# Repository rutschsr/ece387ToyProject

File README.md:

# ECE 387 Individual Final Project
## Overview
This useless box is entirely 3D printed and uses a Arduino Micro (ATMEGA 32U) programmed in C using AVR-GCC and AVRDUDE. 

The operation of the Useless Box toy is very simple ... there are two switches, and when each of them are turned on, an arm emerges from inside the box and turns it back off. Therefore the Useless Box serves no real function: it is "useless".

## Operational Demonstration

## Operational Overview

The Useless box is a simple toy; it turns the switch off when it is turned on by a user. 

## 3D Printed Parts

I designed all of the mechanical parts for the Useless Box in Autodesk Fusion 360. All of the design files are located in this [Folder](https://github.com/rutschsr/ece387ToyProject/tree/main/3-D%20Parts). Each part was "sliced" (split into layers and 3D printer gcode) using [Utlimaker Cura](https://ultimaker.com/software/ultimaker-cura). I then printed each of the pieces on my Creality Ender 3 V2 3D printer using PLA (polyactic acid) filament. Each piece is is hollow and includes between 40 and 60% fill in a triangular manner to reduce print time and increase strength.

### Box Bottom

Box in Autodesk Fusion 360. I exported the drawing to Utilimaker Cura to "slice" it before it was printed.

A raspberry pi running Octoprint is connected to my printer which provides a web interface to upload drawings and control the printer from. This printer is connected to the raspberry pi using a micro usb cable.

The bottom of the box used nearly the entire print volume of the printer, took approximately 22 hours to complete, and used approximately 200g ($4-5) of material.

### Box Top

The top of the Useless box, still on the printer. The larger holes are where the switches are mounted, and the smaller holes are screw holes.

### Box Door

The box with hinge mounts on the printer. The raised area on the bottom was originally planned to be a rubber band mount to close the door, but this was not necessary as the door closes by itself.

### Servo Mount

The original small servo mount with a servo motor. This motor did not have enough torque and was replaced with a larger motor. The design of the Servo mount stayed the same design but was slightly larger.

### Servo Arm

The brackets and arms also took some trial and error to get correct. The larger servo motors meant that the arms had to be offset to turn off the switches, as the box was not wide enough. This was the only real design change with the arm. I used screws to attach the arm to a mount that came with the servo. This just relies on friction between the gears to stay.

## Assembly

Servo Motors mounted inside The Box with switches and offset arms installed. From this view the width of the servo motors and box that required the arms to offset can be seen.

Assembled box with the door open.

## Wiring and Connections

Above is the Schematic Diagram showing the connections for the Useless Box.

My Useless Box accepts a 5-7 V input on either the VIN jack on the outside of the box near the power switch, or the internal battery box which holds four AA batteries.

Internally, the servo motors are powered directly from the VIN port with no voltage regulation and this is why the input is limited to 7 volts. The Arduino Micro is then powered through its VIN pin. On the Arduino two digital input pins are used for the switches, and two PWM pins are used to control the servos. The wiring is very simple, with the only components being the servo motors, the switches, and bleed resistors for the switches.

All of the connections are soldered or socketed to improve the reliability. I used a solder perfboard to attach all of the components and header pins for the Arduino and Servo motors.

The Servo headers are on the bottom left of the perfboard, while the black 4 wire cable goes to the switches mounted on the top of the box. After I soldered the components on to the perfboard I used hotglue on all connections to ensure the wires do not break off at their connections.

## Issues

There were several issues and design changes while building the Useless Box. The first was my original choice for servo motor was very small 9g servo motors. After adding a large arm to be able to reach the switch, the motors did not have enough torque to turn the switches off. I than purchased some 20g replacement servos that are much larger and have much more torque. This required other design changes, however. Since the new motors were larger I had to redesign both the servo mounts and the servo arms. The mounts had to sit lower and be longer to fit the larger motor. The Servo arms had to have an offset so the arm would line up with a switch.

Another issue I experienced was with the Arduino. Originally I planned on using an Arduino Uno clone that I had been gifted several years ago. This has the same ATMEGA A328P on the official Arduino Uno, but as is common with the clones, does not have isolation between the USB power supply and board power supply. I found this out the hard way, by having power from my bench power supply applied through the VIN pin and USB power connected for programming. The ATMEGA microcontroller kept functioning but the USB controller failed and lost the ability to communicate. I then switched to a Arduino micro I had sitting around in preperation for a different project which fits much better inside the box but had its own challenges, such as the surface mounted micro USB programming port I managed to tear off the board almost immediately. Thankfully this was easily fixed with some solder and a few minutes of time. The real issue with the Arduino Micro came when it was time to program it in C. Those issues are explained in more detail in the C code section.

The final issue I had was following the input voltage requirements for the Servo motors. Since the servo motors are connected to the VIN connection and voltage is not regulated the voltage must stay within the servo's voltage rating of 4.0-7.2V even though the Arduino is rated for higher voltage. Unfortunately, I did not follow this and connected the Useless box to a 12V power supply I have with the same barrel jack. This did not immediately cause a failure, but one of the servos did eventually fail (and let the smoke out). I replaced the servo with a spare and it has been functioning correctly (at the correct, 5V input) since.

## Arduino Programming

The Arduino (C++) program I used for testing started with the Arduino example code for sweeping the servo motor. It is modified to move the servo motors based on the switch position. The code is located in the [Arduino Folder](https://github.com/rutschsr/ece387ToyProject/tree/main/Arduino/SimpleTest). It uses two counters in the repeating loop part of the program to sweep each of the servos up when the switch was on, and then sweep it down when it was off. This required two for loops as since the servos are sitting opposite each other, they are rotating in the opposite direction. Also included in this code was code to check that the desired position for the Servos was not exceeding what it needed to in order to turn the switches off. This is important because occassionally the arm gets stuck without turning the switch off, especially if the user is being rough with it. If this motor would get stuck it would put a large amount of stress on the mechanical compoenents and servo motors while also having other unexpected behavior. The counter would count until it overflowed, and then the desired Servo position would become very negative, which also is not desired. The Arduino code also just uses the Arduino Servo library and the Servo.write() method to write the desired location to the servo.

## C code

Although not required for this assignment I chose to challenge myself and implement the code in bare metal C code as well. I experienced two main challenges with this; programming the Arduino Micro Atmega A32U from AVRDUDE, since it operates differently then the A328P and implementing PWM on it, since the counters and registers are different then the A328P. The C code is located in the [src folder](https://github.com/rutschsr/ece387ToyProject/tree/main/src). I used the same python script as the labs to compile and program the arduino, although some modifications to the settings for AVR-GCC and avrdude had to be made to accomidate the ATMEGA A32U.

Programming the A32U from AVRDUDE initially proved to be a challenge but I was eventually able to figure out a procedure that was reliable. As with other labs, I started programming using AVRDUDE in an Ubuntu Virtual machine with the Arduino connection passed through from my Windows laptop. This was unreliable because of the procedure for programming, so eventually I decided to program the Arduino solely from a spare laptop I have that runs Ubuntu natively. 

The Arduino Micro's Atmega A32U microcontroller requires a very specific set of steps to be followed. The reset button must be pushed on the board (The Arduino IDE implements this somehow in software, but I was unable to). Then there are 8 seconds to do the remaining steps: The serial port the Arduino is attatched to must be opened at a rate of 1200bps and then immidiatley closed. I accomplished this by using the serial monitor in the Arduino IDE. Then finally the script that compiles and programs the Arduino using avr-gcc and AVRDUDE must be run. This procedure on the native linux machine had a very high success rate.

The second large issue with programming in C was implementing PWM on the A32U in the Arduino Micro. The registers and counters used for PWM on the A32U are different than those used in the Atmega A328P we used in the labs. I first tried to set up PWM the same was using the different counter configuration for the A32U but this proved time consuming and did not work. I was Thankfully able to find help [Online](https://extremeelectronics.co.in/avr-tutorials/servo-motor-control-by-using-avr-atmega32-microcontroller/) where others had implemented PWM on the Atmega A32U.

With those two issues solved, the rest of the C code is essentially ported from the Arduino Code version. The only differences are syntax and the obvious lack of the Servo.write() method. The C-Code version of the code is what is used for the demonstration video.

## Power Reduction Techniques:
As this project can be battery powered, power reduction techniques are necessary to ensure a long battery life. The useless box can be powered by 4AA batteries in a battery case that is under the useless box door. The box's ATMEGA A32U microcontroller - integrated into the Arduino Micro, is programmed using baremetal C in order to reduce the overhead and power consumption. This also uses direct manipulation of counters for PWM control so any overhead required by the Arduino libraries was eliminated. The battery life is still quite poor however, as the Servo motors can draw approximately 1 amp each under load. When operating under battery power, the AA batteries cannot output 2A for a long period of time, so battery life is poor.

## Improvements:
As with any project, by the time it was finished there were several things that I would do differently if I were to do the project again. One of these changes would be further improving the power consumption. Even with the power reduction techniques described above the power consumption and battery life are still rather poor. One easy power reduction technique I would employ if starting again is controlling the power to the servo motors using a MOSFET, so they would only have power when they are active and have a reason to be moving. Another power reduction technique I would have employed is using interrupts for the switch control, so the microcontroller could be in a ultra low power state when niether of the servos are moving. Finally instead of using the Arduino micro with the ATMEGA 32U microcontroller, I likely would use a bare ATMEGA A328P for the better packaging and power consumption.

Other power improvments for the box could include a rechargable battery system. A rechargable lithium battery could be implemented into the system power it for longer periods of time. This also could be implemented with a USB power source to easier find a power source versus the DC barrel jack on the current Useless Box. As a sidenote, the barrel jack is necessary without a permanant onboard battery due to the high power requirements of the servos that a USB power supply (especially a computer) cannot support.

Mechanical improvements I would make if I were starting again would be to design the bottom of the box with the servo mounts intergrated. This would increase the servo mounts structual integrity, would reduce their movement, and remove the need for the hot glue I added to keep the motors from moving. I also would use screws to mount the servo "arms" to the servo motors instead of relying on friction of the gears to work. While designing the initial bottom of the box I should have also considered the motion of the door opening so that I would not have had to knotch the door on the sides to let it open. This was the first project I had completed with 3-D printed parts and Fusion 360, so it was a learning expierence both with the 3-D design software and my 3-D printer.

## Cost

Cost breakdown. Costs for 3D printed parts are estimated from the slicer's estimate of the filament required for printing.

| Part | Quantity | Cost | Note |
| --- | ----------- | --- | --- |
| Box Bottom | 1 | $5.74 | PLA |
| Box Top | 1 | $1.10 | PLA |
| Box Door | 1 | $1.02 | PLA |
| Servo Arms | 2 | $0.55 | PLA |
| Servo Mounts | 2 | $0.55 | PLA |
| Original Servos| 2 | $10.99 |  |
| Larger Servos| 2 | $22.35 |  |
| Switches | 2 | $1.60 |  |
| Arduino Micro | 1 | $21.00 |  |
| Perfboard | 1 | $6.99 | Adafruit |
| Hinge Rod | 1 | $8.51 |  |
| Miscelaneous | N/A | $5 | Other Various Parts |

Total: $85.40

## More Information:

Additional Documentation found at: https://srutschilling.net/ECE387/ToyProject/

(Site will be undergoing maintenance between May 15-June 1 2022)

Additional help with PWM on ATMEGA 32U from: https://extremeelectronics.co.in/avr-tutorials/servo-motor-control-by-using-avr-atmega32-microcontroller/

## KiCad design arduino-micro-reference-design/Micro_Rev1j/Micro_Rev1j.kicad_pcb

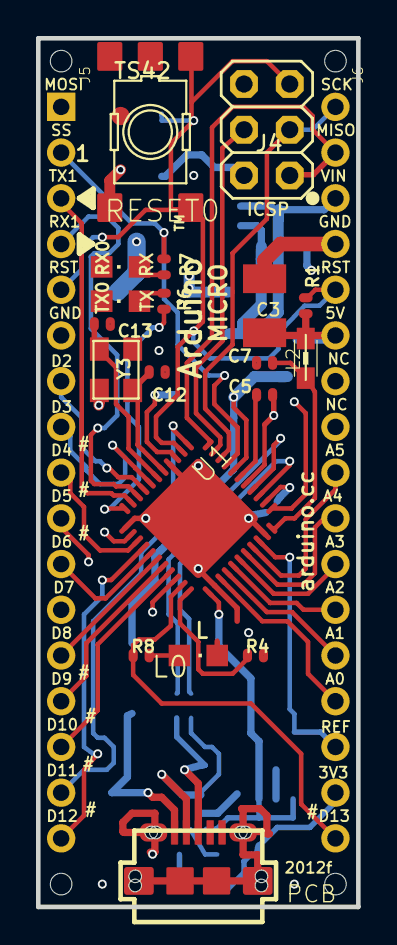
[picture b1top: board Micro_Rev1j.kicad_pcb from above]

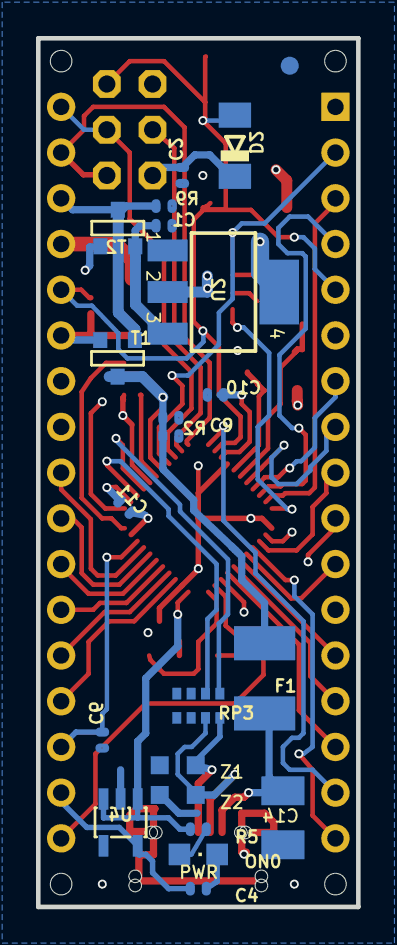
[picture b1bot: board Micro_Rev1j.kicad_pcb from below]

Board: 4 copper layers, 17.8 x 48.3 mm, 49 parts (22 on the bottom side), 47 nets.

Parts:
@HOLE0, @HOLE1, @HOLE2, @HOLE3: (no value)
C1, C2, C6, C9, C10, C11: 100n; C0402
C3, C14: 22u; SMC_B
C4, C5, C7: 1uF; C0402
C12, C13: 22pF; C0402
D2: CD1206-S01575; MINIMELF
F1: MF-MSMF050-2 500mA; L1812
FRAME1: DNP; FRAME
J3: USB-MICRO!!!; CON2_USB_MICRO_B_AT
J4: 3x2M; 2X03
J5: HEAD17-NOSS
J6: HEAD17-NOSS-1
L0: green; CHIPLED_0805
L2: MH2029-300Y; 0805
ON0: blue; CHIPLED_0805
R1, R2, R4, R9: 10K; R0402
R5, R6, R7, R8: 1K; R0402
RESET0: TS42
RP3: 22R; CAY16
RX0: yellow; CHIPLED_0805
T1: FDN340P/PMV48XP; SOT-23
T2: PMV48XP; SOT-23
TX0: yellow; CHIPLED_0805
U1: ATMEGA32U4-XUMU; QFN44ML7X7
U2: NCP1117-5; SOT223
U4: LP2985-33DBVR; SOT23-DBV
U$37: FIDUCIALMOUNT; FIDUCIA-MOUNT
U$53: FIDUCIAL1X2; FIDUCIAL-1X2
Y3: 16MHz KX-7; CRYSTAL-3.2-2.5
Z1, Z2: CG0603MLC-05E; CT_CN0603

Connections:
3V3: C4.1, J6.16, U4.5
+5V: C2.1, C3.+, C10.1, C11.1, D2.C, J4.2, J6.6, L2.1, R1.1, R5.1, T1.2, T2.3, U1.2, U1.14, U1.24, U1.34, U2.2, U2.4, U4.1, U4.3
+VIN: C1.1, T2.2, U2.3
A0: J6.14, U1.36
A1: J6.13, U1.37
A2: J6.12, U1.38
A3: J6.11, U1.39
A4: J6.10, U1.40
A5: J6.9, U1.41
AREF: C6.1, J6.15, U1.42
AVCC: C7.1, L2.2, U1.44
D0/RX: J5.4, U1.20
D1/TX: J5.3, U1.21
D2/SDA: J5.7, U1.19
D3/SCL: J5.8, U1.18
D4*: J5.9, U1.25
D5*: J5.10, U1.31
D6*: J5.11, U1.27
D7: J5.12, U1.1
D+: J3.P3, RP3.8, Z1.1
D-: J3.P2, RP3.7, Z2.1
GND: C1.2, C2.2, C3.-, C4.2, C5.2, C6.2, C7.2, C9.2, C10.2, C11.2, C12.1, C13.1, C14.-, J3.P5, J3.S1, J3.S2, J3.S3, J3.S4, J3.S5, J3.S6, J4.6, J5.6, J6.4, L0.C, ON0.C, R2.1, R4.2, R9.1, RESET0.3, RESET0.4, RESET0.5, RP3.3, RP3.4, RP3.5, RP3.6, RX0.C, TX0.C, U1.5, U1.15, U1.23, U1.35, U1.43, U1.EXP, U2.1, U4.2, Y3.2, Y3.4, Z1.2, Z2.2
HWB: R4.1, U1.33
IO8: J5.13, U1.28
IO9*: J5.14, U1.29
IO10*: J5.15, U1.30
IO11*: J5.16, U1.12
IO12*: J5.17, U1.26
IO13*: J6.17, R8.1, U1.32
MISO: J4.1, J6.2, U1.11
MOSI: J4.4, J5.1, U1.10
unnamed: R7.2, RX0.A
unnamed: ON0.A, R5.2
unnamed: R6.2, TX0.A
unnamed: L0.A, R8.2
RD+: RP3.1, U1.4
RD-: RP3.2, U1.3
RESET: D2.A, J4.5, J5.5, J6.5, R1.2, RESET0.1, RESET0.2, U1.13
RXLED/SS: J5.2, R7.1, U1.8
SCK: J4.3, J6.1, U1.9
TXLED: R6.1, U1.22
UCAP: C5.1, U1.6
VIN: J6.3, R9.2, T1.3, T2.1
VUSB: C9.1, F1.2, R2.2, T1.1, U1.7
VUSBD: C14.+, F1.1, J3.P1
XTAL1: C13.2, U1.17, Y3.3
XTAL2: C12.2, U1.16, Y3.1

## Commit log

2022-03-08 Add STL
    add STL files for some of the 3D printed parts
2022-03-13 Add Remaining 3-D print files
2022-03-14 Test programs
2022-03-14 Some working files
2022-03-14 change files
2022-03-15 Update SimpleTest.ino
    Add some new behavior to fix errors with counters running too high
2022-03-15 More files
2022-03-18 Images
2022-03-27 Switch Test
2022-03-27 Switch Testing
2022-03-27 PWM work
2022-03-27 PWM working
2022-03-27 From C working
2022-03-27 Programming Video Done
2022-04-21 Add some arduino micro PCB files
2022-05-11 Revert "Update README.md"
    This reverts commit 0cd38ab30cf889160bd0160889b56d3378f24090.
2022-05-11 Revert "Revert "Update README.md""
    This reverts commit 1f208bfd1514dc548159613b5b0417e0e6cfea7f.
2022-05-11 Revert "Update README.md"
    This reverts commit 16cbef639d6ecdb2ed3ff1e53dc8744d54f0566a.
